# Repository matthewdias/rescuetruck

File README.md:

# Rescue Truck
 Uniform stagger minivan drop-in pcb

Availability: [Ringer Keys](https://ringerkeys.com/products/rescue-trucks)

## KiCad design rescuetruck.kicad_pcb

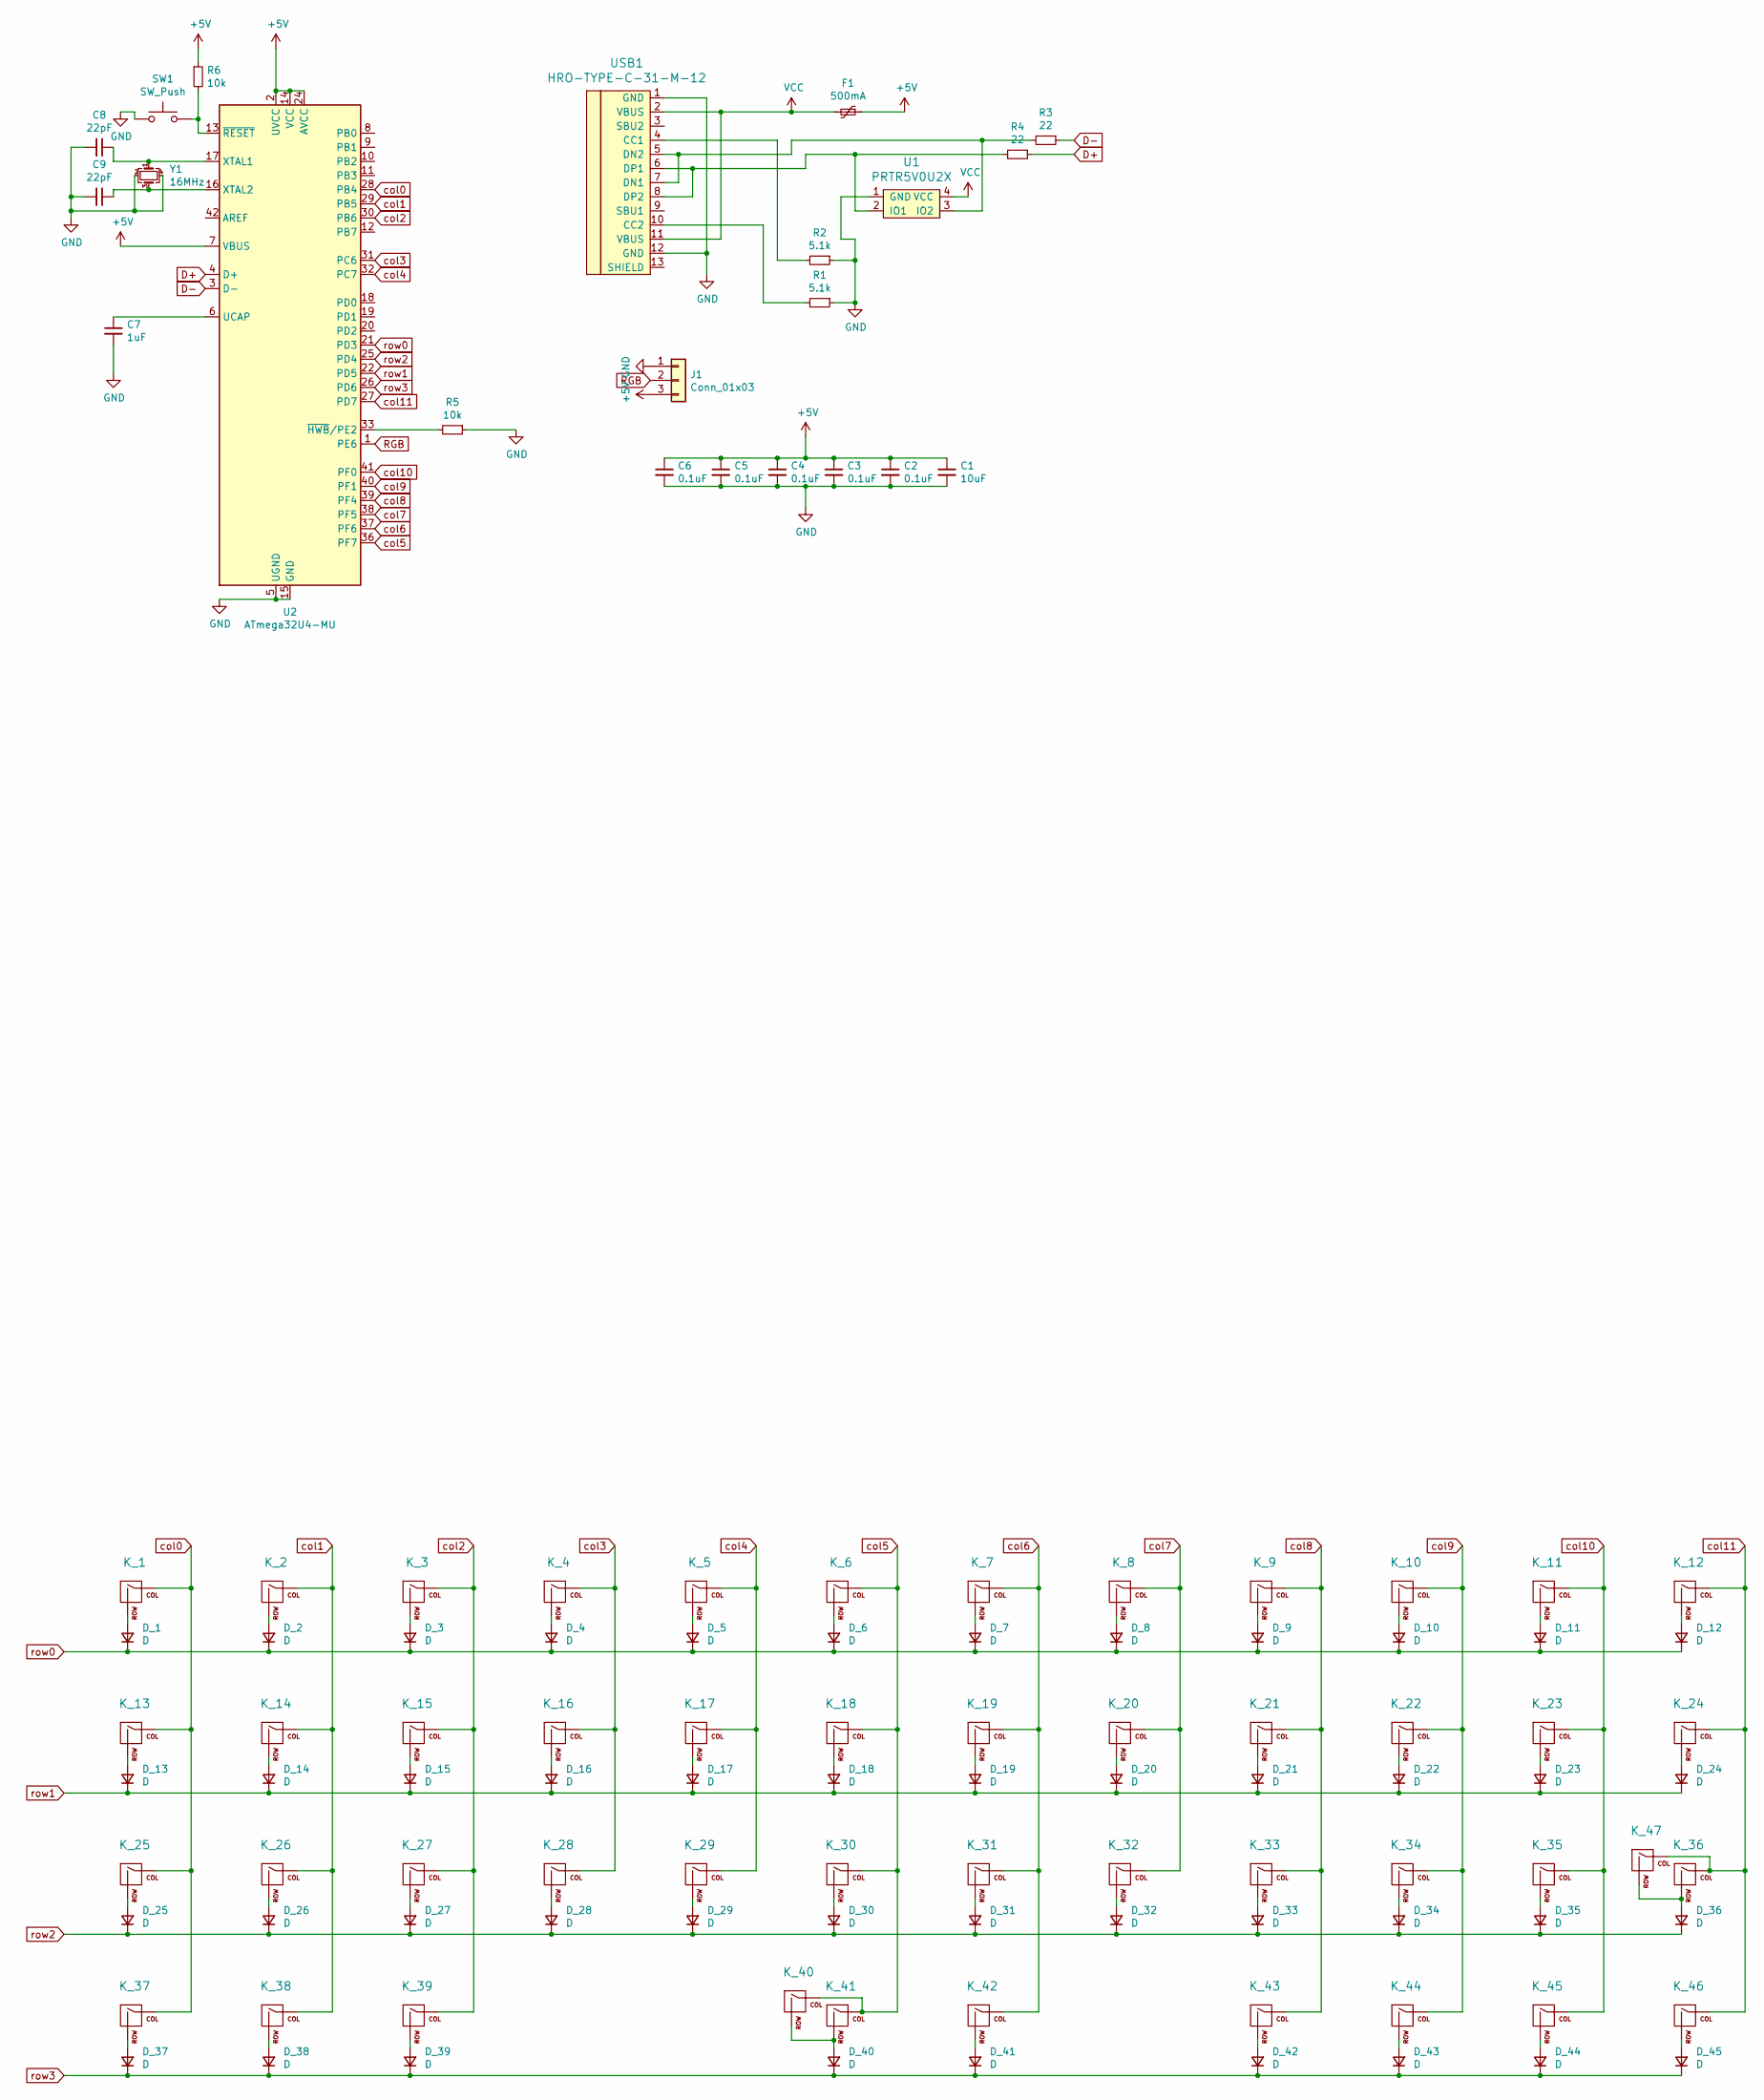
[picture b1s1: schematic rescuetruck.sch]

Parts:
C1: 10uF; C_0603_1608Metric
C2, C3, C4, C5, C6: 0.1uF; C_0603_1608Metric
C7: 1uF; C_0603_1608Metric
C8, C9: 22pF; C_0603_1608Metric
D_1, D_2, D_3, D_4, D_5, D_6, D_7, D_8, D_9, D_10, D_11, D_12, D_13, D_14, D_15, D_16, D_17, D_18, D_19, D_20, D_21, D_22, D_23, D_24, D_25, D_26, D_27, D_28, D_29, D_30, D_31, D_32, D_33, D_34, D_35, D_36, D_37, D_38, D_39, D_40, D_41, D_42, D_43, D_44, D_45: D; D_SOD-123
F1: 500mA; Fuse_1206_3216Metric
J1: Conn_01x03; PinHeader_1x03_P2.54mm_Vertical
K_1, K_2, K_3, K_4, K_5, K_6, K_7, K_8, K_9, K_10, K_11, K_14, K_15, K_16, K_17, K_18, K_19, K_20, K_21, K_22, K_23, K_26, K_27, K_28, K_29, K_30, K_31, K_32, K_33, K_34, K_35, K_44, K_45, K_46: KEYSW; MXOnly-1U-NoLED
K_12: KEYSW; MXOnly-1.75U-NoLED
K_13, K_36, K_37, K_39: KEYSW; MXOnly-1.25U-NoLED
K_24, K_25, K_38, K_43: KEYSW; MXOnly-1.5U-NoLED
K_40: KEYSW; MXOnly-2.25U-ReversedStabilizers-NoLED
K_41: KEYSW; MXOnly-7U-ReversedStabilizers-NoLED
K_42: KEYSW; MXOnly-2U-ReversedStabilizers-NoLED
K_47: KEYSW; MXOnly-ISO-ReversedStabilizers
R1, R2: 5.1k; R_0603_1608Metric
R3, R4: 22; R_0603_1608Metric
R5, R6: 10k; R_0603_1608Metric
SW1: SW_Push; SKQG-1155865
U1: PRTR5V0U2X; SOT143B
U2: ATmega32U4-MU; QFN-44-1EP_7x7mm_P0.5mm_EP5.2x5.2mm
USB1: HRO-TYPE-C-31-M-12; HRO-TYPE-C-31-M-12-Assembly
Y1: 16MHz; Crystal_SMD_3225-4Pin_3.2x2.5mm

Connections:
+5V: C1.1, C2.1, C3.1, C4.1, C5.1, C6.1, F1.1, J1.3, R6.1, U2.2 (UVCC), U2.7 (VBUS), U2.14 (VCC), U2.24 (AVCC), U2.34 (VCC), U2.44 (AVCC)
D+: R4.1, U2.4 (D+)
D-: R3.1, U2.3 (D-)
GND: C1.2, C2.2, C3.2, C4.2, C5.2, C6.2, C7.2, C8.2, C9.2, J1.1, R1.1, R2.1, R5.1, SW1.1, U1.1 (GND), U2.5 (UGND), U2.15 (GND), U2.23 (GND), U2.35 (GND), U2.43 (GND), U2.45 (GND), USB1.1 (GND), USB1.12 (GND), Y1.2, Y1.4
unnamed: C7.1, U2.6 (UCAP)
unnamed: C8.1, U2.17 (XTAL1), Y1.1
unnamed: C9.1, U2.16 (XTAL2), Y1.3
unnamed: D_1.2 (A), K_1.2 (ROW)
unnamed: D_2.2 (A), K_2.2 (ROW)
unnamed: D_3.2 (A), K_3.2 (ROW)
unnamed: D_4.2 (A), K_4.2 (ROW)
unnamed: D_5.2 (A), K_5.2 (ROW)
unnamed: D_6.2 (A), K_6.2 (ROW)
unnamed: D_7.2 (A), K_7.2 (ROW)
unnamed: D_8.2 (A), K_8.2 (ROW)
unnamed: D_9.2 (A), K_9.2 (ROW)
unnamed: D_10.2 (A), K_10.2 (ROW)
unnamed: D_11.2 (A), K_11.2 (ROW)
unnamed: D_12.2 (A), K_12.2 (ROW)
unnamed: D_13.2 (A), K_13.2 (ROW)
unnamed: D_14.2 (A), K_14.2 (ROW)
unnamed: D_15.2 (A), K_15.2 (ROW)
unnamed: D_16.2 (A), K_16.2 (ROW)
unnamed: D_17.2 (A), K_17.2 (ROW)
unnamed: D_18.2 (A), K_18.2 (ROW)
unnamed: D_19.2 (A), K_19.2 (ROW)
unnamed: D_20.2 (A), K_20.2 (ROW)
unnamed: D_21.2 (A), K_21.2 (ROW)
unnamed: D_22.2 (A), K_22.2 (ROW)
unnamed: D_23.2 (A), K_23.2 (ROW)
unnamed: D_24.2 (A), K_24.2 (ROW)
unnamed: D_25.2 (A), K_25.2 (ROW)
unnamed: D_26.2 (A), K_26.2 (ROW)
unnamed: D_27.2 (A), K_27.2 (ROW)
unnamed: D_28.2 (A), K_28.2 (ROW)
unnamed: D_29.2 (A), K_29.2 (ROW)
unnamed: D_30.2 (A), K_30.2 (ROW)
unnamed: D_31.2 (A), K_31.2 (ROW)
unnamed: D_32.2 (A), K_32.2 (ROW)
unnamed: D_33.2 (A), K_33.2 (ROW)
unnamed: D_34.2 (A), K_34.2 (ROW)
unnamed: D_35.2 (A), K_35.2 (ROW)
unnamed: D_36.2 (A), K_36.2 (ROW), K_47.2 (ROW)
unnamed: D_37.2 (A), K_37.2 (ROW)
unnamed: D_38.2 (A), K_38.2 (ROW)
unnamed: D_39.2 (A), K_39.2 (ROW)
unnamed: D_40.2 (A), K_40.2 (ROW), K_41.2 (ROW)
unnamed: D_41.2 (A), K_42.2 (ROW)
unnamed: D_42.2 (A), K_43.2 (ROW)
unnamed: D_43.2 (A), K_44.2 (ROW)
unnamed: D_44.2 (A), K_45.2 (ROW)
unnamed: D_45.2 (A), K_46.2 (ROW)
unnamed: R1.2, USB1.10 (CC2)
unnamed: R2.2, USB1.4 (CC1)
unnamed: R3.2, U1.3 (IO2), USB1.5 (DN2), USB1.7 (DN1)
unnamed: R4.2, U1.2 (IO1), USB1.6 (DP1), USB1.8 (DP2)
unnamed: R5.2, U2.33 (~HWB~/PE2)
unnamed: R6.2, SW1.2, U2.13 (~RESET)
RGB: J1.2, U2.1 (PE6)
VCC: F1.2, U1.4 (VCC), USB1.2 (VBUS), USB1.11 (VBUS)
col0: K_1.1 (COL), K_13.1 (COL), K_25.1 (COL), K_37.1 (COL), U2.28 (PB4)
col1: K_2.1 (COL), K_14.1 (COL), K_26.1 (COL), K_38.1 (COL), U2.29 (PB5)
col2: K_3.1 (COL), K_15.1 (COL), K_27.1 (COL), K_39.1 (COL), U2.30 (PB6)
col3: K_4.1 (COL), K_16.1 (COL), K_28.1 (COL), U2.31 (PC6)
col4: K_5.1 (COL), K_17.1 (COL), K_29.1 (COL), U2.32 (PC7)
col5: K_6.1 (COL), K_18.1 (COL), K_30.1 (COL), K_40.1 (COL), K_41.1 (COL), U2.36 (PF7)
col6: K_7.1 (COL), K_19.1 (COL), K_31.1 (COL), K_42.1 (COL), U2.37 (PF6)
col7: K_8.1 (COL), K_20.1 (COL), K_32.1 (COL), U2.38 (PF5)
col8: K_9.1 (COL), K_21.1 (COL), K_33.1 (COL), K_43.1 (COL), U2.39 (PF4)
col9: K_10.1 (COL), K_22.1 (COL), K_34.1 (COL), K_44.1 (COL), U2.40 (PF1)
col10: K_11.1 (COL), K_23.1 (COL), K_35.1 (COL), K_45.1 (COL), U2.41 (PF0)
col11: K_12.1 (COL), K_24.1 (COL), K_36.1 (COL), K_46.1 (COL), K_47.1 (COL), U2.27 (PD7)
row0: D_1.1 (K), D_2.1 (K), D_3.1 (K), D_4.1 (K), D_5.1 (K), D_6.1 (K), D_7.1 (K), D_8.1 (K), D_9.1 (K), D_10.1 (K), D_11.1 (K), D_12.1 (K), U2.21 (PD3)
row1: D_13.1 (K), D_14.1 (K), D_15.1 (K), D_16.1 (K), D_17.1 (K), D_18.1 (K), D_19.1 (K), D_20.1 (K), D_21.1 (K), D_22.1 (K), D_23.1 (K), D_24.1 (K), U2.22 (PD5)
row2: D_25.1 (K), D_26.1 (K), D_27.1 (K), D_28.1 (K), D_29.1 (K), D_30.1 (K), D_31.1 (K), D_32.1 (K), D_33.1 (K), D_34.1 (K), D_35.1 (K), D_36.1 (K), U2.25 (PD4)
row3: D_37.1 (K), D_38.1 (K), D_39.1 (K), D_40.1 (K), D_41.1 (K), D_42.1 (K), D_43.1 (K), D_44.1 (K), D_45.1 (K), U2.26 (PD6)

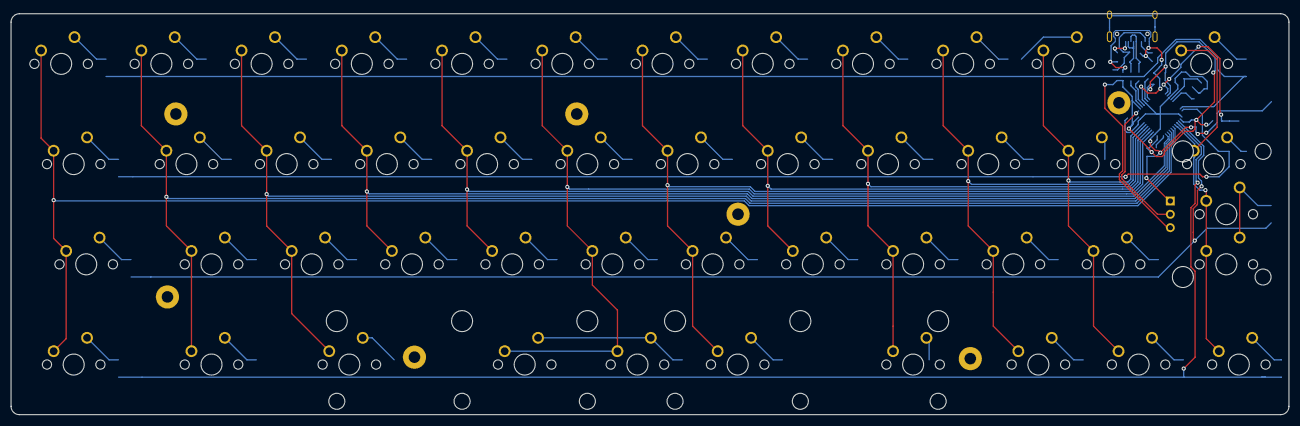
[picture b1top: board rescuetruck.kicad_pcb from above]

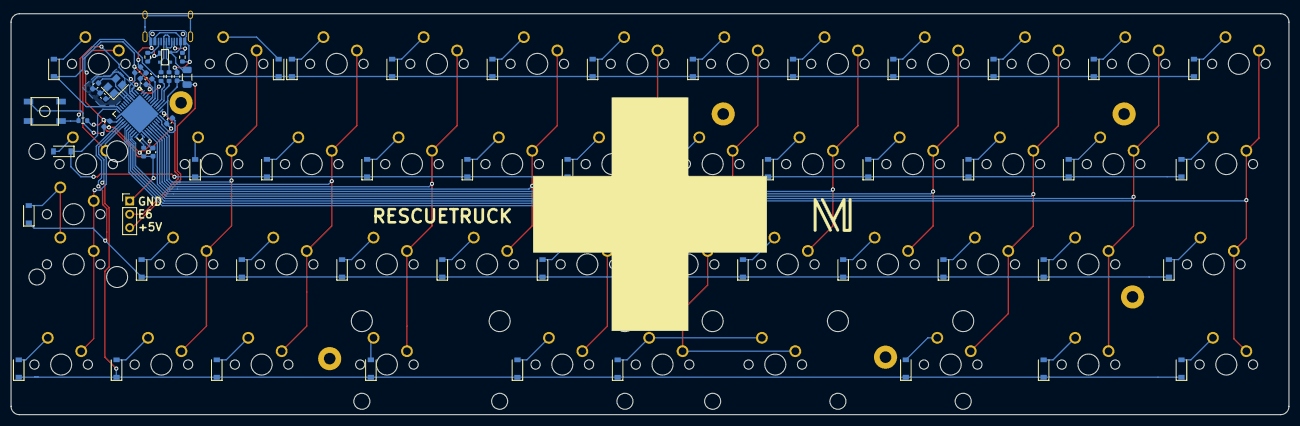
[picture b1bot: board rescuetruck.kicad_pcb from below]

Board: 2 copper layers, 242.9 x 76.2 mm, 121 parts (67 on the bottom side), 76 nets.

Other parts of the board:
H1, H2, H3, H3#2, H4, H5, H6: MountingHole_Pad; MountingHole_2.2mm_M2_Pad

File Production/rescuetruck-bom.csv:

"Designator","Quantity",Value,Footprint,LCSC Part #
"C1, ","1",10uF,0603,C19702
"C2, C3, C4, C5, C6, ","5",0.1uF,0603,C14663
"C7, ","1",1uF,0603,C15849
"C8, C9, ","2",22pF,0603,C1653
"D_1, D_2, D_3, D_4, D_5, D_6, D_7, D_8, D_9, D_10, D_11, D_12, D_13, D_14, D_15, D_16, D_17, D_18, D_19, D_20, D_21, D_22, D_23, D_24, D_25, D_26, D_27, D_28, D_29, D_30, D_31, D_32, D_33, D_34, D_35, D_36, D_37, D_38, D_39, D_40, D_41, D_42, D_43, D_44, D_45, ","45",D,SOD-123,C64898
"F1, ","1",500mA,1206,C70076
"R1, R2, ","2",5.1k,0603,C23186
"R3, R4, ","2",22,0603,C23345
"R5, R6, ","2",10k,0603,C25804
"SW1, ","1",SW_Push,,C318884
"U1, ","1",PRTR5V0U2X,SOT143B,C12333
"U2, ","1",ATmega32U4-MU,QFN-44-1EP 7x7mm,C112161
"USB1, ","1",HRO-TYPE-C-31-M-12,,C165948
"Y1, ","1",16MHz,3225,C13738

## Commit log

2023-05-14 Add project files
2023-05-14 Unignore production files
